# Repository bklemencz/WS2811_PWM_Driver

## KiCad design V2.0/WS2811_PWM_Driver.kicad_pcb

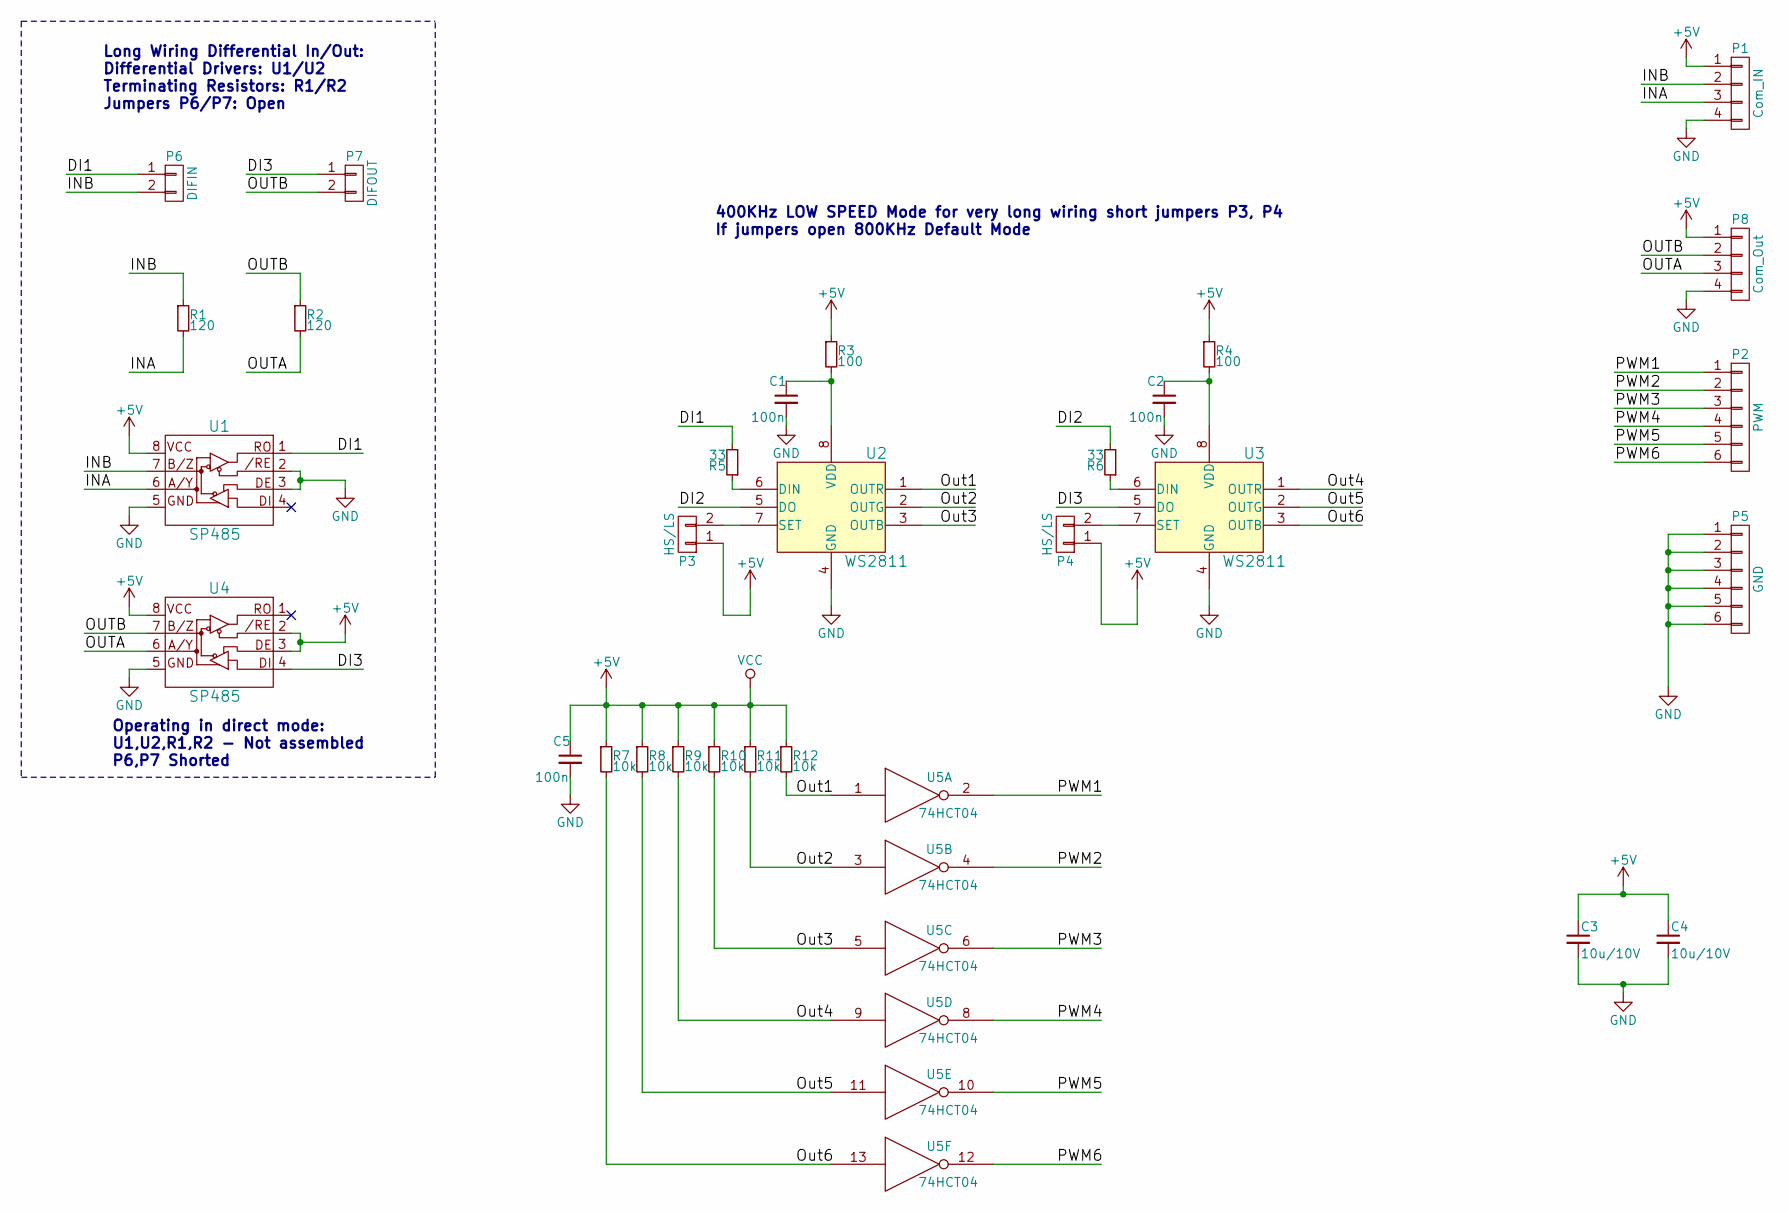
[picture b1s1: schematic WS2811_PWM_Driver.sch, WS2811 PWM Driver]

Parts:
C1, C2, C5: 100n; C_0805
C3, C4: 10u/10V; C_0805
P1: Com_IN; Pin_Header_Straight_1x04_Pitch2.00mm
P2: PWM; Pin_Header_Straight_1x06_Pitch2.00mm
P3, P4: HS/LS; 2_pin_solder_jumper_smd
P5: GND; Pin_Header_Straight_1x06_Pitch2.00mm
P6: DIFIN; 2_pin_solder_jumper_smd
P7: DIFOUT; 2_pin_solder_jumper_smd
P8: Com_Out; Pin_Header_Straight_1x04_Pitch2.00mm
R1, R2: 120; R_0805
R3, R4: 100; R_0805
R5, R6: 33; R_0805
R7, R8, R9, R10, R11, R12: 10k; R_0805
U1, U4: SP485; SOIC-8_3.9x4.9mm_Pitch1.27mm
U2, U3: WS2811; SOIC-8_3.9x4.9mm_Pitch1.27mm
U5: 74HCT04; SOIC-14_3.9x8.7mm_Pitch1.27mm

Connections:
+5V: C3.1, C4.1, C5.1, P1.1, P3.1, P4.1, P8.1, R3.1, R4.1, R7.1, R8.1, R9.1, R10.1, R11.1, R12.1, U1.8 (VCC), U4.2 (/RE), U4.3 (DE), U4.8 (VCC), U5.14 (VCC)
/DI1: P6.1, R5.2, U1.1 (RO)
/DI2: R6.2, U2.5 (DO)
/DI3: P7.1, U3.5 (DO), U4.4 (DI)
/INA: P1.3, R1.2, U1.6 (A/Y)
/INB: P1.2, P6.2, R1.1, U1.7 (B/Z)
/OUTA: P8.3, R2.2, U4.6 (A/Y)
/OUTB: P7.2, P8.2, R2.1, U4.7 (B/Z)
/Out1: R12.2, U2.1 (OUTR), U5.1
/Out2: R11.2, U2.2 (OUTG), U5.3
/Out3: R10.2, U2.3 (OUTB), U5.5
/Out4: R9.2, U3.1 (OUTR), U5.9
/Out5: R8.2, U3.2 (OUTG), U5.11
/Out6: R7.2, U3.3 (OUTB), U5.13
/PWM1: P2.1, U5.2
/PWM2: P2.2, U5.4
/PWM3: P2.3, U5.6
/PWM4: P2.4, U5.8
/PWM5: P2.5, U5.10
/PWM6: P2.6, U5.12
GND: C1.2, C2.2, C3.2, C4.2, C5.2, P1.4, P5.1, P5.2, P5.3, P5.4, P5.5, P5.6, P8.4, U1.2 (/RE), U1.3 (DE), U1.5 (GND), U2.4 (GND), U3.4 (GND), U4.5 (GND), U5.7 (GND)
unnamed: C1.1, R3.2, U2.8 (VDD)
unnamed: C2.1, R4.2, U3.8 (VDD)
unnamed: P3.2, U2.7 (SET)
unnamed: P4.2, U3.7 (SET)
unnamed: R5.1, U2.6 (DIN)
unnamed: R6.1, U3.6 (DIN)

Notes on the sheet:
Long Wiring Differential In/Out: Differential Drivers: U1/U2 Terminating Resistors: R1/R2 Jumpers P6/P7: Open
400KHz LOW SPEED Mode for very long wiring short jumpers P3, P4 If jumpers open 800KHz Default Mode
Operating in direct mode: U1,U2,R1,R2 - Not assembled P6,P7 Shorted

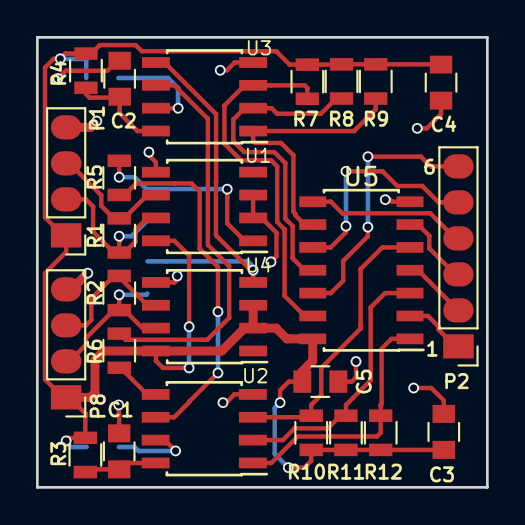
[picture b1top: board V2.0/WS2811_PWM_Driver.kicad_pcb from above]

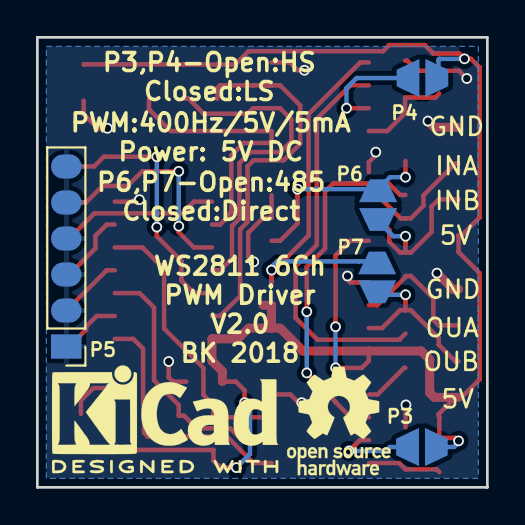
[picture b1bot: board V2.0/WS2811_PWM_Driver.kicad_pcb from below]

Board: 2 copper layers, 25.0 x 25.0 mm, 30 parts (5 on the bottom side), 27 nets.

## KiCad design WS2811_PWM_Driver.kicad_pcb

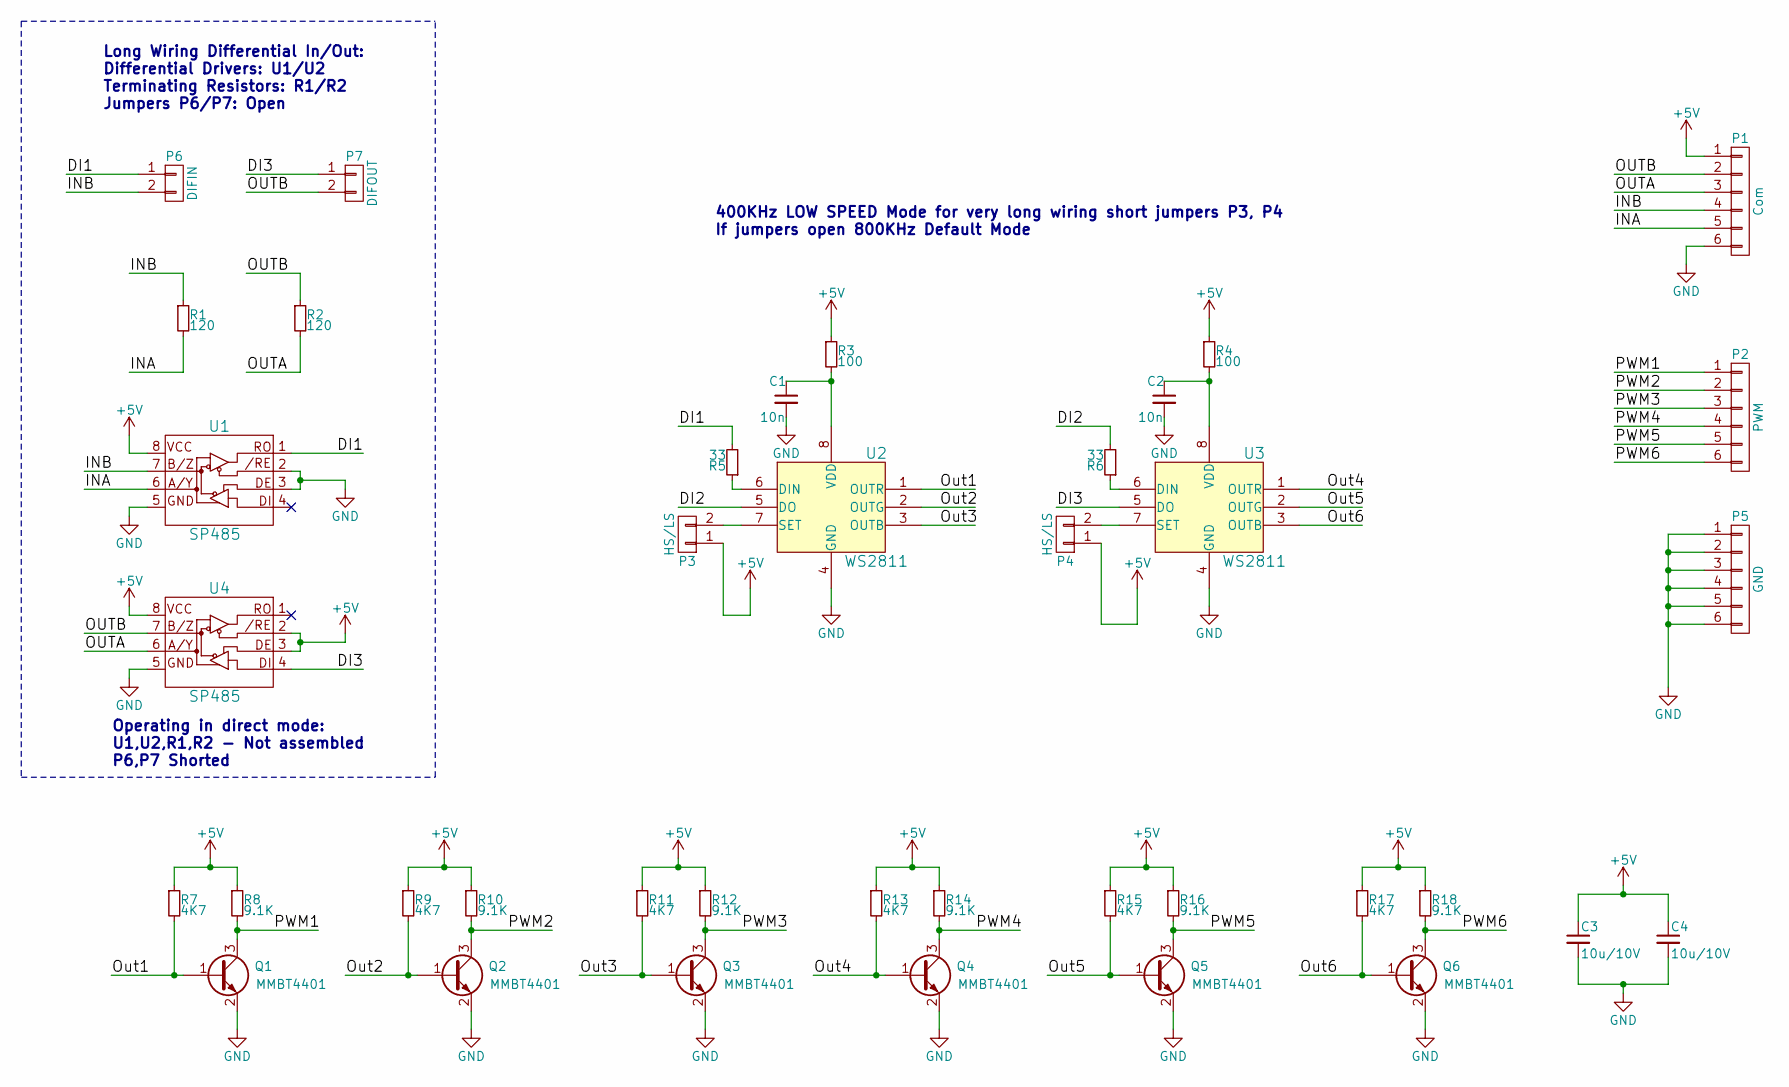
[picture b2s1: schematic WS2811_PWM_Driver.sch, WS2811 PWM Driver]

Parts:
C1, C2: 10n; C_0805
C3, C4: 10u/10V; C_0805
P1: Com; Pin_Header_Straight_1x06_Pitch2.00mm
P2: PWM; Pin_Header_Straight_1x06_Pitch2.00mm
P3, P4: HS/LS; 2_pin_solder_jumper_smd
P5: GND; Pin_Header_Straight_1x06_Pitch2.00mm
P6: DIFIN; 2_pin_solder_jumper_smd
P7: DIFOUT; 2_pin_solder_jumper_smd
Q1, Q2, Q3, Q4, Q5, Q6: MMBT4401; SOT-23
R1, R2: 120; R_0805
R3, R4: 100; R_0805
R5, R6: 33; R_0805
R7, R9, R11, R13, R15, R17: 4K7; R_0603
R8, R10, R12, R14, R16, R18: 9.1K; R_0603
U1, U4: SP485; SOIC-8_3.9x4.9mm_Pitch1.27mm
U2, U3: WS2811; SOIC-8_3.9x4.9mm_Pitch1.27mm

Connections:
+5V: C3.1, C4.1, P1.1, P3.1, P4.1, R3.1, R4.1, R7.1, R8.1, R9.1, R10.1, R11.1, R12.1, R13.1, R14.1, R15.1, R16.1, R17.1, R18.1, U1.8 (VCC), U4.2 (/RE), U4.3 (DE), U4.8 (VCC)
/DI1: P6.1, R5.2, U1.1 (RO)
/DI2: R6.2, U2.5 (DO)
/DI3: P7.1, U3.5 (DO), U4.4 (DI)
/INA: P1.5, R1.2, U1.6 (A/Y)
/INB: P1.4, P6.2, R1.1, U1.7 (B/Z)
/OUTA: P1.3, R2.2, U4.6 (A/Y)
/OUTB: P1.2, P7.2, R2.1, U4.7 (B/Z)
/Out1: Q1.1 (B), R7.2, U2.1 (OUTR)
/Out2: Q2.1 (B), R9.2, U2.2 (OUTG)
/Out3: Q3.1 (B), R11.2, U2.3 (OUTB)
/Out4: Q4.1 (B), R13.2, U3.1 (OUTR)
/Out5: Q5.1 (B), R15.2, U3.2 (OUTG)
/Out6: Q6.1 (B), R17.2, U3.3 (OUTB)
/PWM1: P2.1, Q1.3 (C), R8.2
/PWM2: P2.2, Q2.3 (C), R10.2
/PWM3: P2.3, Q3.3 (C), R12.2
/PWM4: P2.4, Q4.3 (C), R14.2
/PWM5: P2.5, Q5.3 (C), R16.2
/PWM6: P2.6, Q6.3 (C), R18.2
GND: C1.2, C2.2, C3.2, C4.2, P1.6, P5.1, P5.2, P5.3, P5.4, P5.5, P5.6, Q1.2 (E), Q2.2 (E), Q3.2 (E), Q4.2 (E), Q5.2 (E), Q6.2 (E), U1.2 (/RE), U1.3 (DE), U1.5 (GND), U2.4 (GND), U3.4 (GND), U4.5 (GND)
unnamed: C1.1, R3.2, U2.8 (VDD)
unnamed: C2.1, R4.2, U3.8 (VDD)
unnamed: P3.2, U2.7 (SET)
unnamed: P4.2, U3.7 (SET)
unnamed: R5.1, U2.6 (DIN)
unnamed: R6.1, U3.6 (DIN)

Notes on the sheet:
Long Wiring Differential In/Out: Differential Drivers: U1/U2 Terminating Resistors: R1/R2 Jumpers P6/P7: Open
400KHz LOW SPEED Mode for very long wiring short jumpers P3, P4 If jumpers open 800KHz Default Mode
Operating in direct mode: U1,U2,R1,R2 - Not assembled P6,P7 Shorted

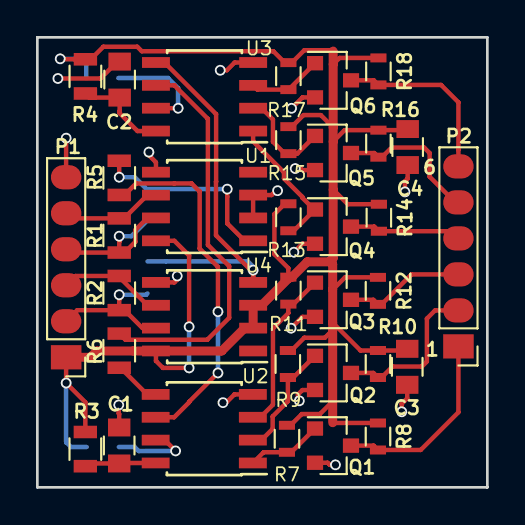
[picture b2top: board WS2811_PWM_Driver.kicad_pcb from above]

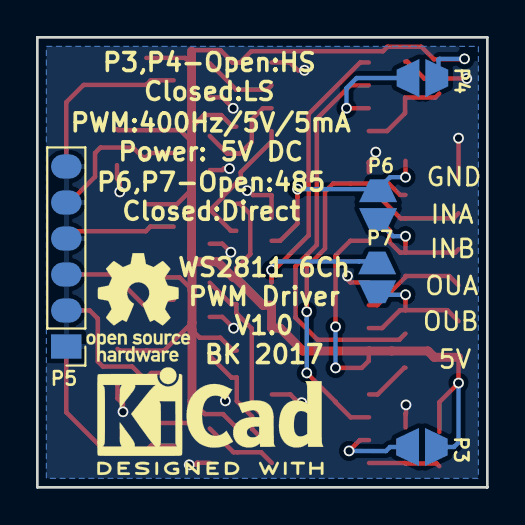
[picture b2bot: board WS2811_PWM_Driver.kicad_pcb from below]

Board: 2 copper layers, 25.0 x 25.0 mm, 39 parts (5 on the bottom side), 27 nets.

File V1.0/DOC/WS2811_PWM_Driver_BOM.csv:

Id,Designator,Package,Quantity,Designation,Supplier and ref
1,"Q3,Q1,Q2,Q4,Q5,Q6",SOT-23,6,MMBT4401,
2,"C1,C2",C_0805,2,10n,
6,"R1,R2",R_0805,2,120,
7,"R3,R4",R_0805,2,100,
8,"R5,R6",R_0805,2,33,
9,"U1,U4",SOIC-8_3.9x4.9mm_Pitch1.27mm,2,SP485,
10,"U2,U3",SOIC-8_3.9x4.9mm_Pitch1.27mm,2,WS2811,
11,"R7,R9,R11,R13,R15,R17",R_0603,6,4K7,
12,"R8,R10,R12,R14,R16,R18",R_0603,6,510,
13,"C3,C4",C_0805,2,10u/10V,

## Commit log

2017-11-07 :confetti_ball: Added .gitattributes & .gitignore files
2017-11-07 Initial
2017-11-08 PCB Update
2017-11-09 PCB_Gerbers
2017-11-12 Gerber Updates
2017-11-12 Add BOM in DOC
2018-01-08 Added V2.0 with HC04 Inverter
